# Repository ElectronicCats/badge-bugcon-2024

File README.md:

# Badge BugCON  2024

Badge Oficial BugCON 2024

## Getting started

1. Connect Badge via USB to your computer.
2. Open the serial port indicated for the badge on your computer through a program such as Arduino IDE, Putty or Screen at 115200 bauds.
3. The badge text should appear in the terminal.

## Tecnologia

### Community
- ESP32C6
- Baterias 2 x AA
- USB
- OLED 128×32 0.91 I2C SSD1306
- LEDS

### VIP
- ESP32C6
- Baterias 2 x AA
- USB
- GC9A01 Display TFT LCD Circular 1.28"
- LEDS

## How to build the firmware Community

Check the [Developer guide](./firmware/README.md) to learn how to build the firmware from scratch.

## How to build the firmware VIP

Check the [Developer guide CircuitPython](https://learn.adafruit.com/welcome-to-circuitpython/overview) to learn how to build the firmware from scratch.

Recommended development IDE [Thonny](https://thonny.org/)

## Gratitude
Do you want to say thank you? Tag these companies on social networks and show them your badge, thanks to them it is possible

- [BugCON Team](https://www.bugcon.org/)
- [ElectronicCats](https://electroniccats.com/)

## License

Electronic Cats invests time and resources providing this open source design, please support Electronic Cats and open-source hardware by purchasing products from Electronic Cats!

Designed by Electronic Cats.

Hardware released under an CERN Open Hardware Licence v1.2. See the LICENSE_HARDWARE file for more information.

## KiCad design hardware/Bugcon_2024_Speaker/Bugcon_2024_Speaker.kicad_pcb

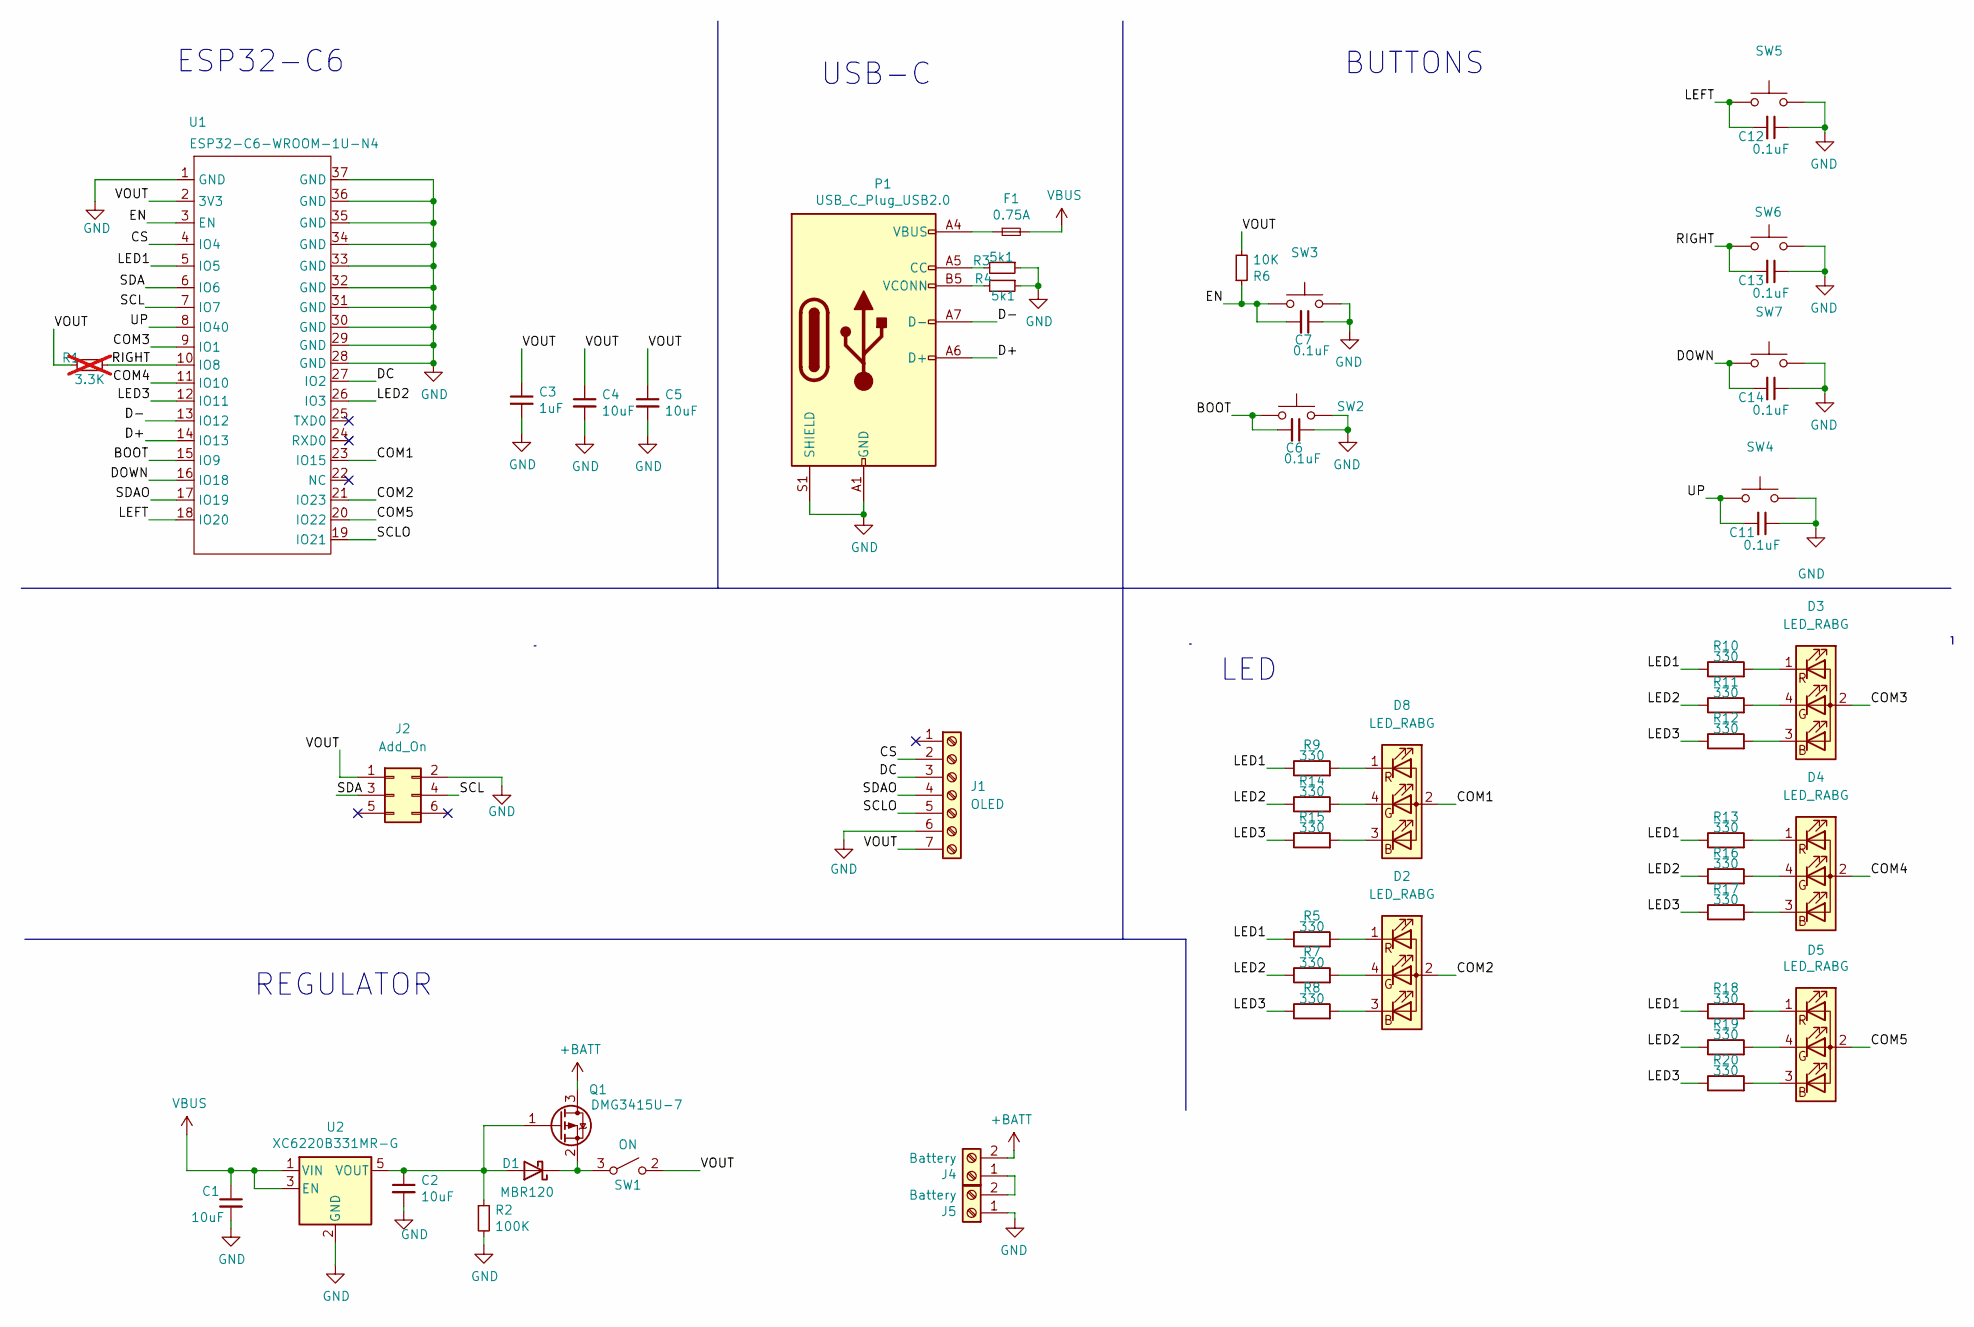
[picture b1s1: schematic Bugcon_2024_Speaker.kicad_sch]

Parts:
C1, C2, C4, C5: 10uF; C_0603_1608Metric; LCSC# C85713
C3: 1uF; C_0603_1608Metric; LCSC# C15849
C6, C7, C11, C12, C13, C14: 0.1uF; C_0603_1608Metric; LCSC# C478888
D1: MBR120; D_SOD-123F; LCSC# C130880
D2, D3, D4, D5, D8: LED_RABG; AAA3528SURKCGKC09
F1: 0.75A; Fuse_0805_2012Metric; LCSC# C1972808
J1: OLED; PinHeader_1x07_P2.54mm_Vertical
J2: Add_On; PinSocket_2x03_P2.54mm_Vertical; LCSC# C5116527
J4, J5: Battery; BATT_8BH-AA-A1AJ020_MYG; LCSC# C5290181
P1: USB_C_Plug_USB2.0; C393939; LCSC# C393939
Q1: DMG3415U-7; SOT-23; LCSC# C96616
R1: 3.3K; R_0603_1608Metric; LCSC# C403480; not fitted
R2: 100K; R_0603_1608Metric; LCSC# C25803
R3, R4: 5k1; R_0603_1608Metric; LCSC# C113390
R5, R7, R8, R9, R10, R11, R12, R13, R14, R15, R16, R17, R18, R19, R20: 330; R_0603_1608Metric; LCSC# C25231
R6: 10K; R_0603_1608Metric; LCSC# C217281
SW1: ON; MSK12C02; LCSC# C431540
SW2, SW3, SW4, SW5, SW6, SW7: SW_SPST_TL3342; LCSC# C318889
U1: ESP32-C6-WROOM-1U-N4; XCVR_ESP32-C6-WROOM-1-N8
U2: XC6220B331MR-G; SOT-23-5; LCSC# C86534

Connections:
+BATT: J4.2, Q1.3 (D)
/BOOT: C6.2, SW2.2, U1.15 (IO9)
/COM1: D8.2 (A), U1.23 (IO15)
/COM2: D2.2 (A), U1.21 (IO23)
/COM3: D3.2 (A), U1.9 (IO1)
/COM4: D4.2 (A), U1.11 (IO10)
/COM5: D5.2 (A), U1.20 (IO22)
/CS: J1.2, U1.4 (IO4)
/D+: P1.A6 (D+), U1.14 (IO13)
/D-: P1.A7 (D-), U1.13 (IO12)
/DC: J1.3, U1.27 (IO2)
/DOWN: C14.2, SW7.2, U1.16 (IO18)
/EN: C7.2, R6.1, SW3.2, U1.3 (EN)
/LED1: R5.1, R9.1, R10.1, R13.1, R18.1, U1.5 (IO5)
/LED2: R7.1, R11.1, R14.1, R16.1, R19.1, U1.26 (IO3)
/LED3: R8.1, R12.1, R15.1, R17.1, R20.1, U1.12 (IO11)
/LEFT: C12.2, SW5.2, U1.18 (IO20)
/RIGHT: C13.2, R1.1, SW6.2, U1.10 (IO8)
/SCL: J2.4, U1.7 (IO7)
/SCLO: J1.5, U1.19 (IO21)
/SDA: J2.3, U1.6 (IO6)
/SDAO: J1.4, U1.17 (IO19)
/UP: C11.2, SW4.2, U1.8 (IO40)
/VOUT: C3.1, C4.1, C5.1, J1.7, J2.1, R1.2, R6.2, SW1.2 (B), U1.2 (3V3)
GND: C1.2, C2.2, C3.2, C4.2, C5.2, C6.1, C7.1, C11.1, C12.1, C13.1, C14.1, J1.6, J2.2, J5.1, P1.A1 (GND), P1.A12 (GND), P1.B1 (GND), P1.B12 (GND), P1.S1 (SHIELD), R2.2, R3.1, R4.1, SW2.1, SW3.1, SW4.1, SW5.1, SW6.1, SW7.1, U1.1 (GND), U1.28 (GND), U1.29 (GND), U1.30 (GND), U1.31 (GND), U1.32 (GND), U1.33 (GND), U1.34 (GND), U1.35 (GND), U1.36 (GND), U1.37 (GND), U2.2 (GND)
unnamed: C2.1, D1.2 (A), Q1.1 (G), R2.1, U2.5 (VOUT)
unnamed: D1.1 (K), Q1.2 (S), SW1.3 (A)
unnamed: D2.3 (BK), R8.2
unnamed: D2.4 (GK), R7.2
unnamed: D2.1 (RK), R5.2
unnamed: D3.3 (BK), R12.2
unnamed: D3.4 (GK), R11.2
unnamed: D3.1 (RK), R10.2
unnamed: D4.3 (BK), R17.2
unnamed: D4.4 (GK), R16.2
unnamed: D4.1 (RK), R13.2
unnamed: D5.3 (BK), R20.2
unnamed: D5.4 (GK), R19.2
unnamed: D5.1 (RK), R18.2
unnamed: D8.3 (BK), R15.2
unnamed: D8.4 (GK), R14.2
unnamed: D8.1 (RK), R9.2
unnamed: F1.1, P1.A4 (VBUS), P1.A9 (VBUS), P1.B4 (VBUS), P1.B9 (VBUS)
unnamed: J4.1, J5.2
unnamed: P1.A5 (CC), R3.2
unnamed: P1.B5 (VCONN), R4.2
VBUS: C1.1, F1.2, U2.1 (VIN), U2.3 (EN)

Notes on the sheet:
BUTTONS
LED
ESP32-C6
REGULATOR
USB-C

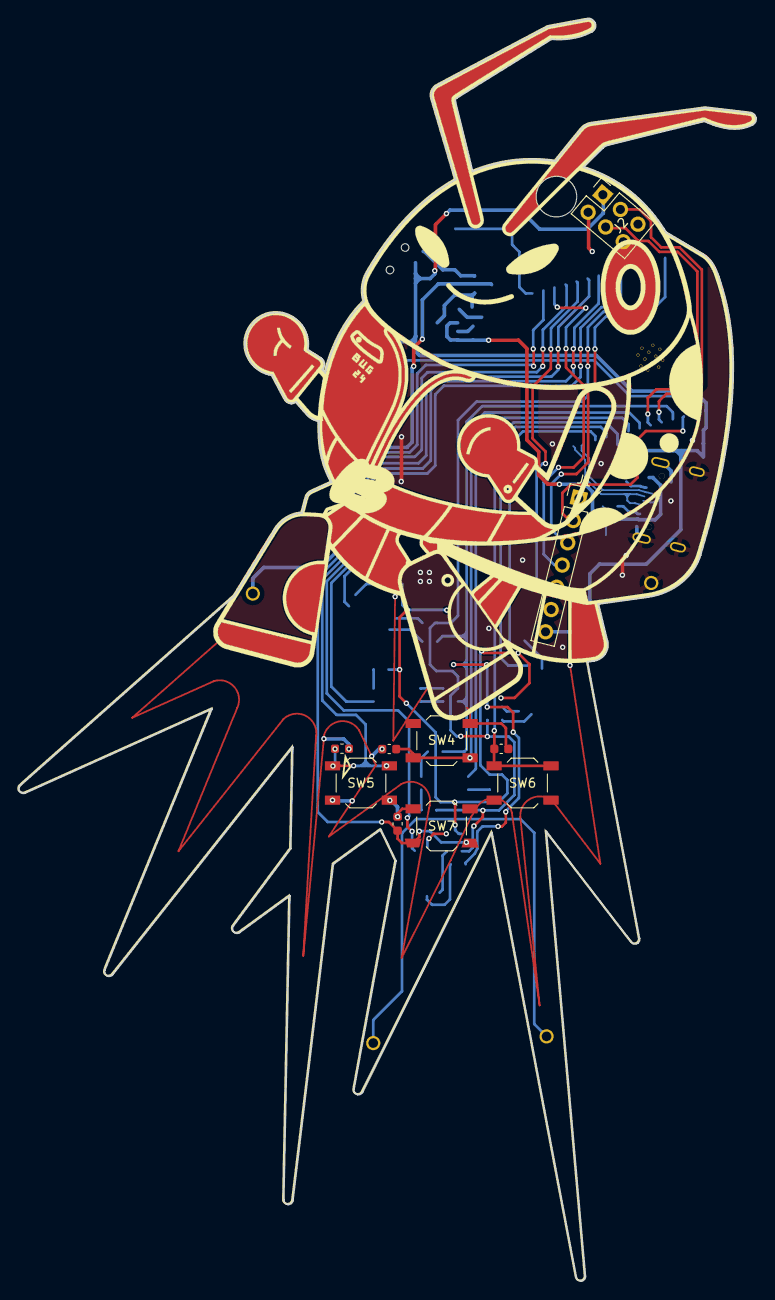
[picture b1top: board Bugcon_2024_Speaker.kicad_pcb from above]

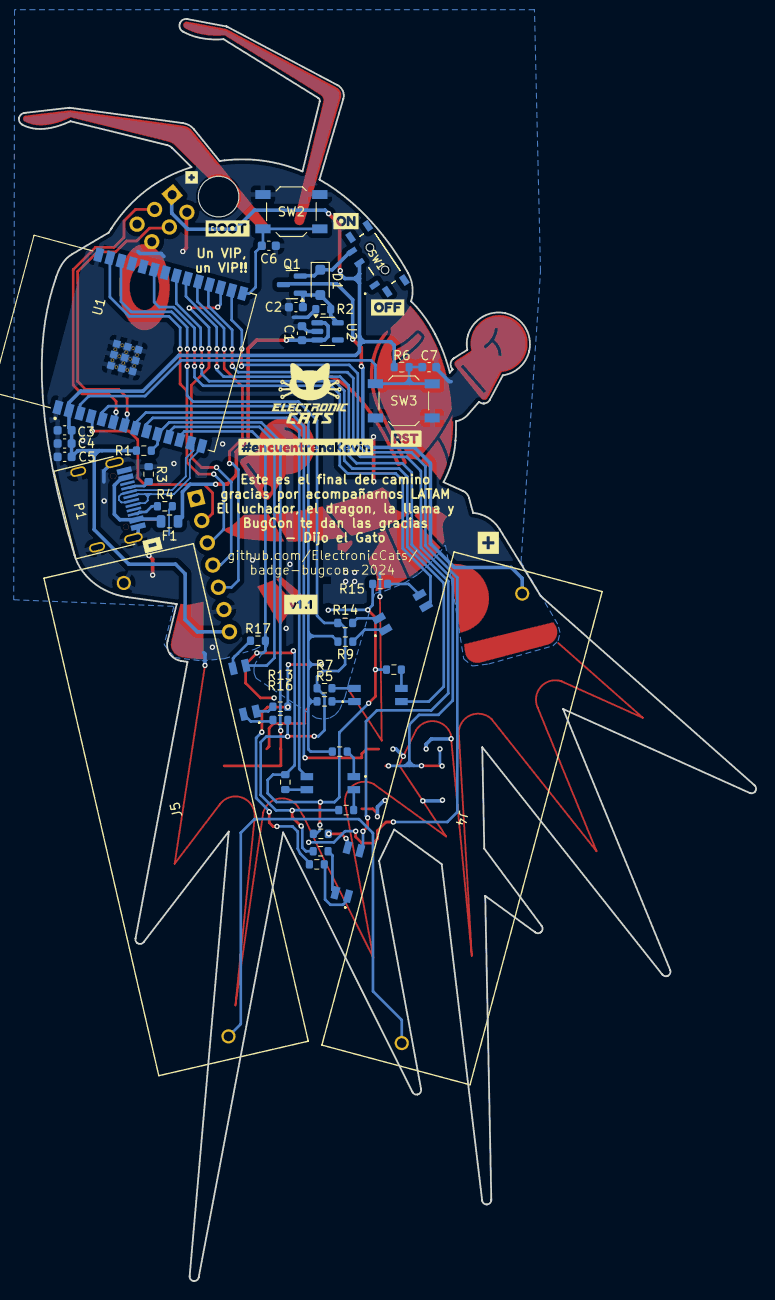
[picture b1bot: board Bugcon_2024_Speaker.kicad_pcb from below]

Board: 2 copper layers, 81.7 x 139.8 mm, 63 parts (52 on the bottom side), 47 nets.

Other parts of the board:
Ref**: Val**; 01.BugCON Personajes-
kibuzzard-66F1E44B: G***; kibuzzard-66F1E44B
kibuzzard-66F1E442: G***; kibuzzard-66F1E442
kibuzzard-66F1E456: G***; kibuzzard-66F1E456
kibuzzard-66F1E462: G***; kibuzzard-66F1E462
kibuzzard-66FD9EC0: G***; kibuzzard-66FD9EC0
kibuzzard-66FD9F77: G***; kibuzzard-66FD9F77
kibuzzard-666C8A00: G***; kibuzzard-666C8A00
kibuzzard-666C89F7: G***; kibuzzard-666C89F7
kibuzzard-670026B6: G***; kibuzzard-670026B6

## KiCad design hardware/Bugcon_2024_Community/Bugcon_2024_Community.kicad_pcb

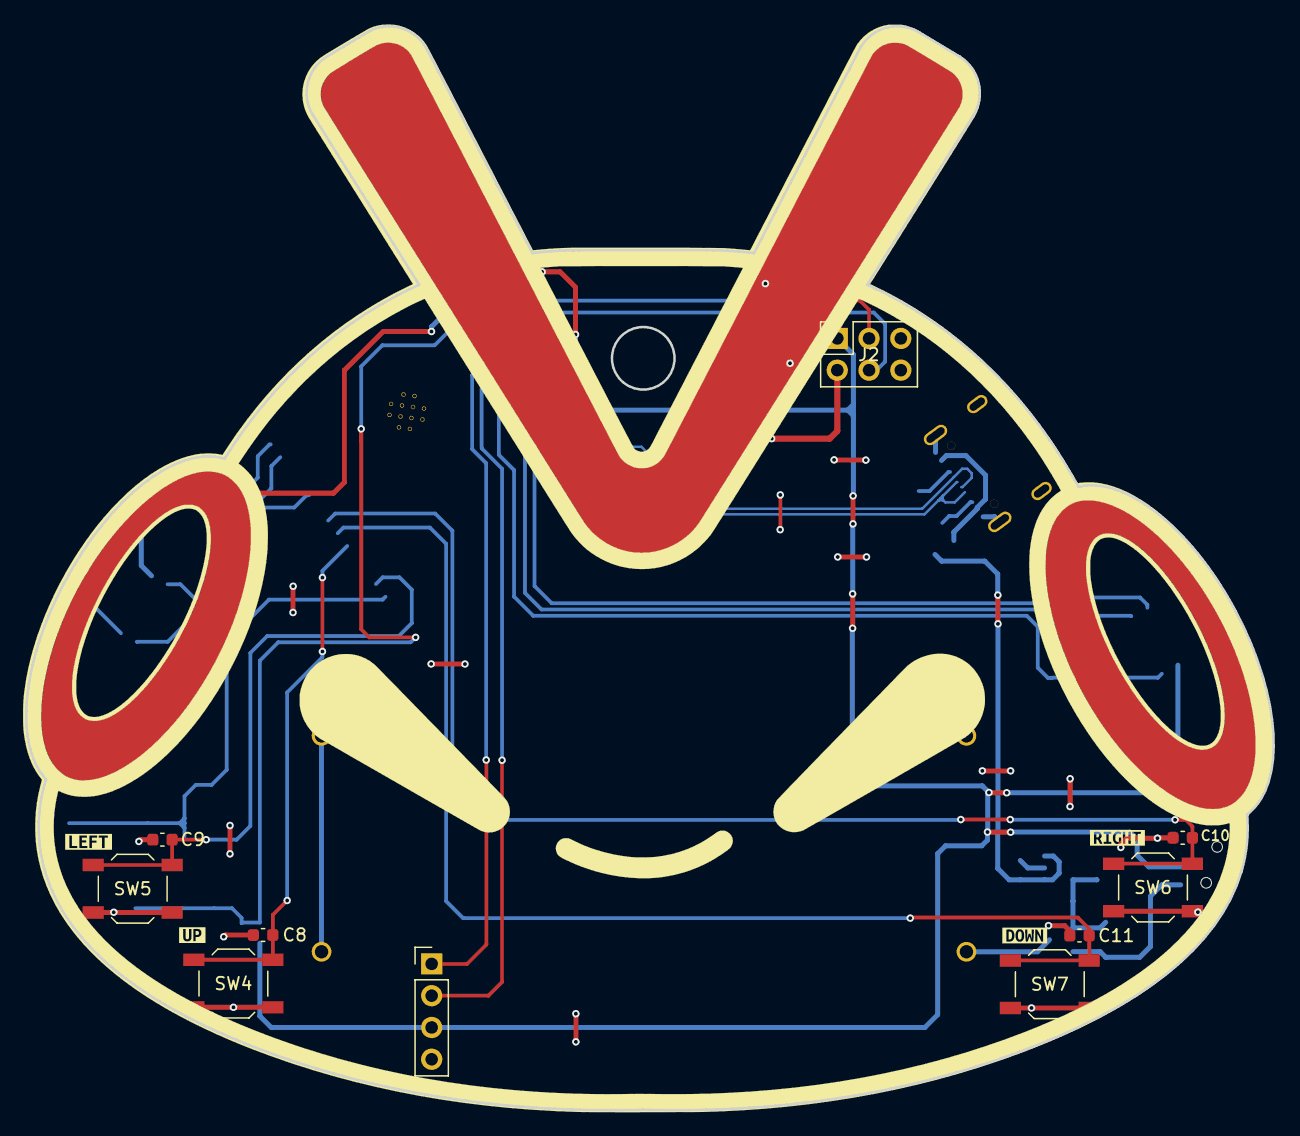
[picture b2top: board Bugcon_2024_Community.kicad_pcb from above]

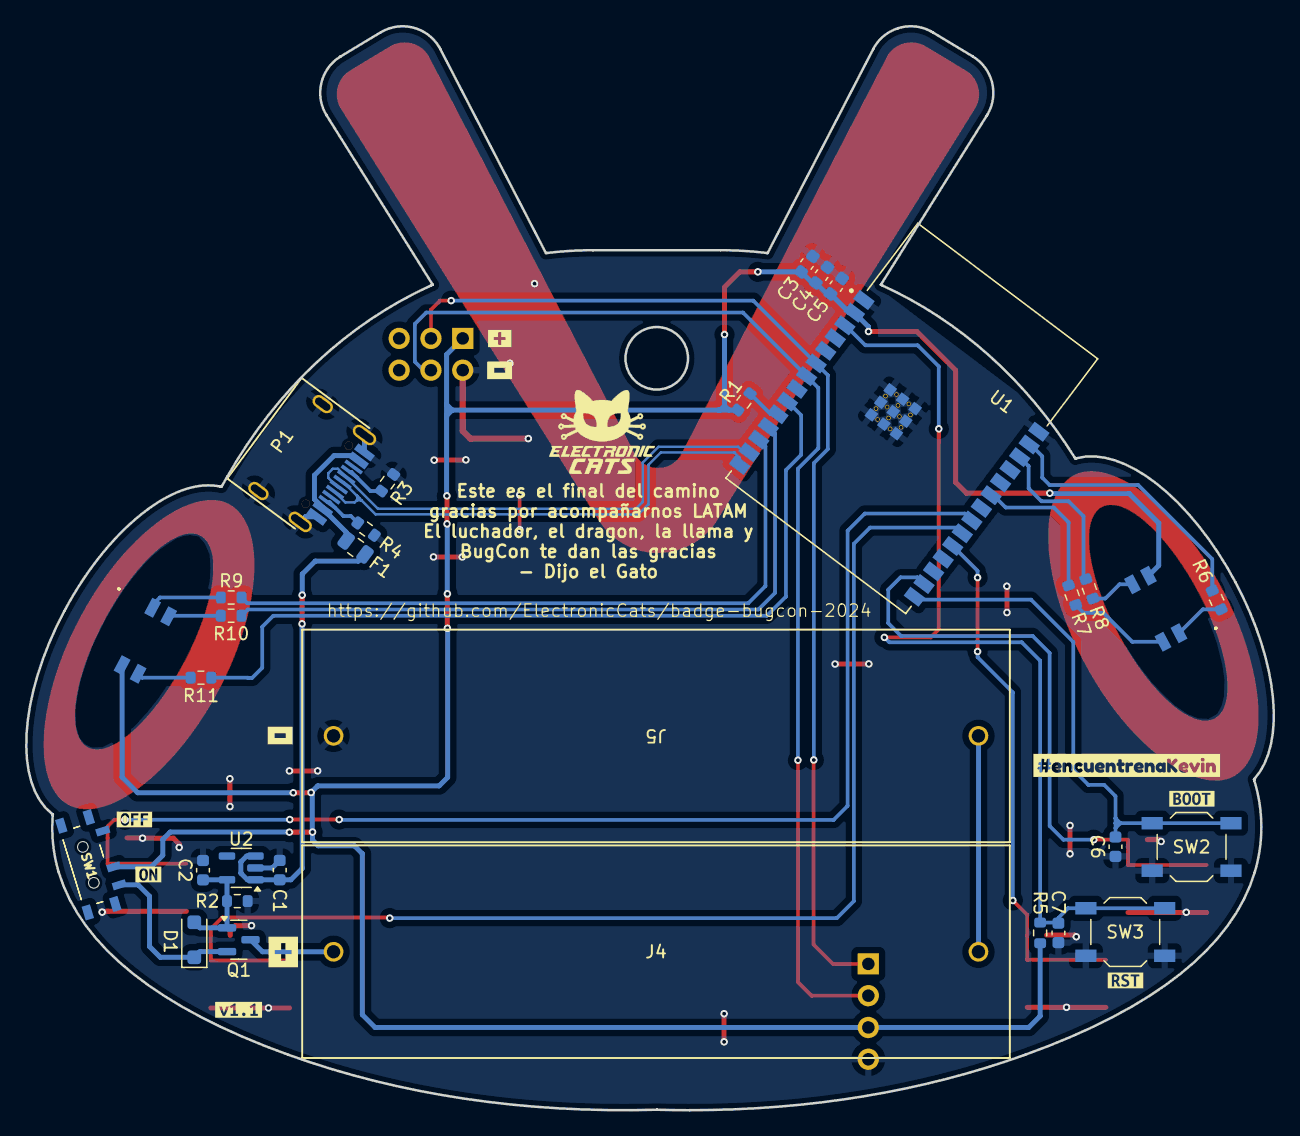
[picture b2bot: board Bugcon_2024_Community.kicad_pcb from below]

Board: 2 copper layers, 99.7 x 86.6 mm, 56 parts (41 on the bottom side), 33 nets.

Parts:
C1, C2, C4, C5: 10uF; C_0603_1608Metric
C3: 1uF; C_0603_1608Metric
C6, C7, C8, C9, C10, C11: 0.1uF; C_0603_1608Metric
D1: MBR120; D_SOD-123F
D2, D3: LED_RABG; AAA3528SURKCGKC09
F1: 0.75A; Fuse_0805_2012Metric
J2: Add_On; PinSocket_2x03_P2.54mm_Vertical
J3: OLED; Display OLED 128 x32
J4, J5: Battery; BATT_8BH-AA-A1AJ020_MYG
P1: USB_C_Plug_USB2.0; C393939
Q1: DMG3415U-7; SOT-23
R1: 3.3K; R_0603_1608Metric
R2: 100K; R_0603_1608Metric
R3, R4: 5k1; R_0603_1608Metric
R5: 10K; R_0603_1608Metric
R6, R7, R8, R9, R10, R11: 330; R_0603_1608Metric
Ref**: Val**; 02.BugCON Personajes
SW1: ON; MSK12C02
SW2, SW3, SW4, SW5, SW6, SW7: SW_SPST_TL3342
U1: ESP32-C6-WROOM-1U-N4; XCVR_ESP32-C6-WROOM-1-N8
U2: XC6220B331MR-G; SOT-23-5
kibuzzard-66F475F7: G***; kibuzzard-66F475F7
kibuzzard-66F4760F: G***; kibuzzard-66F4760F
kibuzzard-66F4761D: G***; kibuzzard-66F4761D
kibuzzard-66F4762A: G***; kibuzzard-66F4762A
kibuzzard-66F47603: G***; kibuzzard-66F47603
kibuzzard-66F47638: G***; kibuzzard-66F47638
kibuzzard-66F47642: G***; kibuzzard-66F47642
kibuzzard-66F47655: G***; kibuzzard-66F47655
kibuzzard-66F47715: G***; kibuzzard-66F47715
kibuzzard-66FD9F77: G***; kibuzzard-66FD9F77
kibuzzard-666C8A00: G***; kibuzzard-666C8A00
kibuzzard-666C89F7, kibuzzard-666C89F7#2: G***; kibuzzard-666C89F7
kibuzzard-6700283A: G***; kibuzzard-6700283A

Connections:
+BATT: J4.2, Q1.3 (D)
/BOOT: C6.2, SW2.2, U1.15 (IO9)
/D+: P1.A6 (D+), U1.14 (IO13)
/D-: P1.A7 (D-), U1.13 (IO12)
/DOWN: C11.2, SW7.2, U1.20 (IO22)
/EN: C7.2, R5.1, SW3.2, U1.3 (EN)
/LED1: R6.1, U1.27 (IO2)
/LED2: R7.1, U1.23 (IO15)
/LED3: R8.1, U1.26 (IO3)
/LED4: R9.1, U1.12 (IO11)
/LED5: R10.1, U1.11 (IO10)
/LED6: R11.1, U1.9 (IO1)
/LEFT: C9.2, SW5.2, U1.16 (IO18)
/RIGHT: C10.2, SW6.2, U1.21 (IO23)
/SCL: J2.4, J3.2, U1.7 (IO7)
/SDA: J2.3, J3.1, U1.6 (IO6)
/UP: C8.2, SW4.2, U1.19 (IO21)
/VOUT: C3.1, C4.1, C5.1, D2.2 (A), D3.2 (A), J2.1, J3.3, R1.2, R5.2, SW1.2 (B), U1.2 (3V3)
GND: C1.2, C2.2, C3.2, C4.2, C5.2, C6.1, C7.1, C8.1, C9.1, C10.1, C11.1, J2.2, J3.4, J5.1, P1.A1 (GND), P1.S1 (SHIELD), R2.2, R3.1, R4.1, SW2.1, SW3.1, SW4.1, SW5.1, SW6.1, SW7.1, U1.1 (GND), U1.28 (GND), U1.29 (GND), U1.30 (GND), U1.31 (GND), U1.32 (GND), U1.33 (GND), U1.34 (GND), U1.35 (GND), U1.36 (GND), U1.37 (GND), U2.2 (GND)
unnamed: C2.1, D1.2 (A), Q1.1 (G), R2.1, U2.5 (VOUT)
unnamed: D1.1 (K), Q1.2 (S), SW1.3 (A)
unnamed: D2.3 (BK), R8.2
unnamed: D2.4 (GK), R7.2
unnamed: D2.1 (RK), R6.2
unnamed: D3.3 (BK), R11.2
unnamed: D3.4 (GK), R10.2
unnamed: D3.1 (RK), R9.2
unnamed: F1.1, P1.A4 (VBUS)
unnamed: J4.1, J5.2
unnamed: P1.A5 (CC), R3.2
unnamed: P1.B5 (VCONN), R4.2
unnamed: R1.1, U1.10 (IO8)
VBUS: C1.1, F1.2, U2.1 (VIN), U2.3 (EN)

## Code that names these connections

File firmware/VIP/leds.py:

import board
import random
import time
import pwmio
from digitalio import DigitalInOut, Direction
import microcontroller

LED1 = 0
LED2 = 1
LED3 = 2
LED4 = 3
LED5 = 4

class RGBLEDS:
    def __init__(self):
        self.red = None
        self.green = None
        self.blue = None
        self.com = []
        self.init()
    
    def init(self, pin_red=board.IO5, pin_green=board.IO3, pin_blue=microcontroller.pin.GPIO11, pin_com_list=[microcontroller.pin.GPIO15, board.IO10, microcontroller.pin.GPIO23, board.IO1, microcontroller.pin.GPIO22]):
        
        self.red = pwmio.PWMOut(pin_red, frequency=1000, duty_cycle=0)
        self.green = pwmio.PWMOut(pin_green, frequency=1000, duty_cycle=0)
        self.blue = pwmio.PWMOut(pin_blue, frequency=1000, duty_cycle=0)

        self.com = [DigitalInOut(pin) for pin in pin_com_list]
        for pin in self.com:
            pin.direction = Direction.OUTPUT
            pin.value = False

        self.set_color([0, 0, 0])
        self.turn_off_all()

    def set_color(self, rgb):
        self.red.duty_cycle = 65535 - rgb[0]
        self.green.duty_cycle = 65535 - rgb[1]
        self.blue.duty_cycle = 65535 - rgb[2]

    def turn_off(self, led):
        if 0 <= led < len(self.com):
            self.com[led].value = False

    def turn_on(self, led):
        if 0 <= led < len(self.com):
            self.com[led].value = True

    def turn_on_all(self):
        for pin in self.com:
            pin.value = True
    
    def turn_off_all(self):
        for pin in self.com:
            pin.value = False
            
    def get_random_color(self):
        r = random.randint(45000, 50000)
        g = random.randint(0, r // 12)
        b = random.randint(0, g // 2) 
        return [r, g, b]
    
    def launch_particles(self, num, delay):
        for _ in range(num):
            for j in range(5):
                self.turn_off_all()
                self.set_color(self.get_random_color())
                self.turn_on(j)
                time.sleep(delay)
        self.turn_off_all()
    
    def launch_animation(self):
        self.launch_particles(1, 0.04)
        time.sleep(0.4)
        self.launch_particles(2, 0.03)
        time.sleep(0.3)
        self.launch_particles(5, 0.03)
        time.sleep(0.3)
        self.launch_particles(15, 0.02)
        self.turn_off_all()

def get_leds_obj():
    global leds_obj
    return leds_obj

def leds_init():
    global leds_obj
    leds_obj = RGBLEDS()
    leds_obj.launch_animation()

if __name__ == "__main__":
    leds_init()

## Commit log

2024-08-14 feat(Hw): Add community and speaker boards
2024-08-22 feat(Hw): Update community PCB
2024-08-22 feat(Hw): Update community route
2024-09-03 feat(Hw): Update route
2024-09-05 feat(Hw):Added_1A_Regulator
2024-09-05 feat(Hw):Connected_Reset_Update_Regulator
2024-09-05 feat(Hw): Update ground areas
2024-09-06 feat(Hw): Change LEDs
2024-09-09 feat(Hw):Update_Route
2024-09-23 fix(hw): fix pins for OLED
2024-09-23 feat: add labels and logos
2024-09-25 feat(Hw):Update_Route_And_Labels
2024-09-27 feat(Hw):Added_Hole_And_Review
2024-09-27 feat(Hw):Update_Labels
2024-09-27 feat(Hw):Moved_Hole_Speaker
2024-10-02 feat: add more labels
2024-10-02 docs: Update README.md
2024-10-04 feat(Hw):Update_Labels_And_route
2024-10-08 feat(Hw):Update_BOM
2024-11-06 feat: add sketch test
2024-11-07 feat: add test community
2024-11-08 feat: add button test
2024-11-15 feat: add fw
2024-11-17 feat: add eko party firmware
2024-11-17 chore: add minino gitignore rules
2024-11-17 feat: add leds animations
2024-11-17 chore: remove local badge connect component
2024-11-17 feat: add badge connect as submodule
2024-11-17 fix: do not count badges already found
2024-11-18 feat: remove ekoparty's exclusive code
2024-11-19 feat: add rgb controller component as submodule
2024-11-19 feat: add leds animation at startup
2024-11-19 fix: use low speed mode
2024-11-19 feat: add bsided games
2024-11-19 fix: old keyboard cb params
2024-11-19 feat: recrease rssi filter for games
2024-11-19 chore: add zip files
2024-11-19 chore: change projecto name to bugcon
2024-11-19 feat: add help instructions for games
2024-11-19 feat: add leds animation every 5 minutes
2024-11-19 feat: add bugcon logo
2024-11-21 feat: add paths firmware
2024-11-21 fix: remove duplicate images
2024-11-21 feat: add images eyes
2024-11-25 refactor: remove git submodules
2024-11-25 fix: typo Update README.md
2025-01-29 feat: Create LICENSE_HARDWARE.md
